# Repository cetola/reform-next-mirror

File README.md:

# MNT Reform Next

The original Open Hardware laptop, reloaded.

## Modular Concept

MNT Reform Next takes the MNT Reform family's modular approach a few steps further: The motherboard doesn't have any exterior ports, instead it breaks out all important signals in groups to FPC and JST-SH headers. The connectivity to the outside is implemented via user-exchangable Port Boards that increase repairability, customizability and future proofing of interfaces. The motherboard provides the system controller (RP2040 based), main (multi chemistry) LiFePO4/LiIon charger buck/boost controller, main 5V and 3V3 power rails and the SOM (Processor Module) interface, as well as a 4-lane PCIe M.2 connector for fast NVMe performance.

## Motherboard

Status: Version D-1 (code named "Reflex") designed, soldered, brought up on 2024-06-21.

Internal connectors:

- USB3+2 to Port Board One
- USB3+2 to Port Board Two
- 1 GBit Ethernet
- SD Card (4-bit)
- I2S Audio
- HDMI
- Display Power and Backlight PWM
- Serial UART for Debug
- Power Interface incl. I2C (for USB-C PD or direct power)
- 2x redundant/parallel Battery Packs (Power, Alert and I2C)
- Internal Keyboard Ports (USB and UART for standby mode)

Additional Features:

- RP2040 system controller
- 4-lane PCIe M.2 connector for NVMe
- RGB status LED
- 8-position DIP switch with several configuration options:
  - Power Override: Power on regardless of system controller output (useful for bringup without firmware)
  - Select battery chemistry/charge voltage (LiFePO4/LiIon)
  - Switch RP2040 USB to either SOM or external port for flashing
- USB2.0 hub
  - to provide enough internal USB2.0 ports for input devices and RP2040 communication

Power System:

- BQ25756 multi-chemistry charge buck/boost controller for 4S2P LiFePO4 or 4S2P LiIon batteries
- LM62460 for 6A of 5V power
- LM62460 for 6A of 3.3V power
- MAX1837EUT33+T for Standby 3v3 power

All main power rails work, and i.MX8MPlus Reform Processor module was used to boot Linux, which was operable via serial console (UART 2):

The system idles with only 2.3W power draw with the i.MX8MPlus module, meeting or power efficiency goals.

Motherboards physically fits in the prototype 3D printed case from december 2023:

## Processor Modules

MNT Reform Next supports a [variety of Processor Modules](https://mntre.com/modularity.html). The standard module is the RCORE with 8-core Rockchip RK3588 processor and Mali G610 GPU: https://source.mnt.re/reform/mnt-reform-rk3588-som/#mnt-reform-rcore-rk3588-som

## Port Boards

3 in total: Left, Right and Back sides:

- Standard Port Board One:
  - USB-C with USB3+2 signalling and USB Power Delivery
  - 1 GBit Ethernet (ix Industrial. Device will be shipped with a short ix to RJ45 jack dongle.)
  - MicroSD slot (bootable)
  - TLV320AIC3100 Soundchip with internal speaker driver/connector
  - Headset TRRS jack (stereo headphone driver and mono microphone support)
- Standard Port Board Two:
  - Full-size HDMI
  - 2x USB-C with USB3+2 signalling
  - 1x USB-A with USB3+2 signalling for legacy USB devices
- Standard Port Board Three:
  - WiFi/BT chipset and antennas

### Port Board One Dimensions / Specs

Port Board One is mounted on the left side of the case and is responsible for USB-C Power Delivery. When customizing this board, this functionality must be retained for powering the laptop. Copy the KiCAD source files as a starting point. There is a mechanical/spatial coupling with the keyboard that rests above the ports. Please take a look at the following drawing to see where the keyboard PCB is cut away. This defines the space that is available for ports. Any parts and connectors should not be taller than x mm above a 1.6mm PCB, because keycaps could collide with the components when being pressing down.

The electrical interfaces normally available to the left side are:

### Port Board Two Dimensions / Specs

Port Board Two is mounted on the right side of the case and mainly provides USB connectivity (3 ports), plus HDMI. Copy the KiCAD source files as a starting point. A similar mechanical/spatial coupling with the keyboard as with the Port Board One constrains the port placement, see the following drawing.

The electrical interfaces normally available to the right side are:

### Port Board Three Dimensions / Specs

Port Board Three hosts a WiFi/BT chipset by default. It receives USB2, SDIO and UART (with flow control) signals as well as 5V and 3V3 power from Processor Modules that support this (like the RCORE RK3588 module).

The default WiFi/BT implementation is based around the Ezurio Sterling-LWB5+ WiFi 5 with Bluetooth 5.2 SMT module. The chipset is Cypress CYW4373EUBGT, which has good Linux mainline driver support.

By default, this board doesn't expose any connectors to the outside. Instead, WiFi/BT antennas are mounted on it, and the port cover is made from an RF transmissive material to allow for good reception. But you can customize this board while making use of the available space under/behind the keyboard to add external ports, like external antenna connectors, or back-facing USB.

The electrical interfaces normally available to the back side are:

### Area Below the Keyboard

You have up to four millimeters of vertical space below the keyboard for extending port boards with low-profile components. 1mm or 0.8mm thick PCBs are recommended. You can also create boards that splice/transform/forward available FFC signals, such as USB (with hubs), I2C (with extenders), Ethernet (switch), etc. as long as they fit under the keyboard. There is some more space available between the through-hole pin rows of the keyboard. It is recommended to load your design as a STEP model into the provided FreeCAD laptop assembly file to check for any mechanical interference.

## Battery System

In Reform Next, the battery packs have 4 user replacable 18650 cells in series each. The packs are connected to the motherboard in parallel, so they are fully redundant. They have their own monitoring and balancing circuits and abstract all measurements like cell voltages, current, and alert states digitally over I2C. The main buck/boost charger resides on the motherboard. The coordination of the packs, the charger, and the USB-C power delivery living on Port Board one are implemented centrally in free software running on the RP2040 microcontroller on the motherboard. The default chemistry of the cells is LiFePO4. The chemistry can be switched to LiIon using DIP switches on the motherboard--this optional user choice trades longer runtime for less safety and environmental friendliness.

At the current state of development, the laptop successfully runs a Linux Wayland desktop from a single or two inserted battery packs. The small OLED display on top of the keyboard can show individual cell voltages and system voltage as well as dis/charging current.

The battery packs can be charged via USB-C power delivery from a off-the-shelf charger using the USB-C port on the left of the device.

## Case

The case, designed by Ana Dantas, has passed several revisions and is now (2024-09-24) ready for ordering as aluminum CNC milled parts.

- The case bottom integrates grooves to hold 8x 18650 batteries split into two parallel packs.
- The case bottom, as a large aluminum body, acts as the main heatsink for the CPU. The motherboard with CPU is mounted upside down with the CPU conducting heat to the case through a thermal pad. The motherboard is symmetrical and can also be flipped so that the CPU is on top, making it easier to work on the device for debugging.
- The case bottom also features a metric grid of screw threads for mounting standard and user defined electronics, a feature inspired by the "Peek array" in the original Novena OSHW laptop.
- The screen back integrates pockets for installing a camera module and mounting points for a FPC to JST-SH cable converter for the camera module.

## Mechanical Keyboard

The keyboard is an evolution/redesign of MNT Reform Keyboard V3 and integrates Pocket Reform features like RGB backlight and upgraded controller (RP2040). Keyswitches are Kailh Choc and keycaps are customized MBK Glows by FKcaps.

## Trackpad

The trackpad is an evolution of the multitouch glass trackpad option for classic MNT Reform based on the Azoteq TPS65 with IQS550 sensor. We revised it with a bigger, seamless frosted glass cover for which we sampled multiple glass suppliers and selected the one with the best haptics. We also added a strip of 3 mouse buttons below the trackpad to offer an alternative to multi finger gestures, including a middle mouse button that is important on Linux/BSD/Plan 9 desktops. The buttons are ultra low profile mechanical switches: Cherry MX ULP. As there are no commercially available keycaps for these switches, we developed our own based on the resources at [https://github.com/pashutk/Cherry_MX_ULP](https://github.com/pashutk/Cherry_MX_ULP).

## Camera Module

We developed the electronics of our OSHW standalone USB camera into a new version that can be installed inside of the MNT Reform Next. The sensor with autofocus lens is installed in a cavity in the screen back case above the display. The screen front part has a 2mm hole that the camera can look through. Below the display sits an adapter PCB that converts the flat/flex cable of the image sensor for a JST-SH based cable that transmits the MIPI-CSI signal through the right hinge of the laptop. A camera acquisition PCB that is part of the camera kit can be installed on the 4x4cm mounting grid below the keyboard. This converts the camera video signal into standard USB 3 or 2 UVC for use by the main processor. This module also has a connector for a hard powerdown switch and a LED that shows if it is powered. 

## Credits (So Far)

- Ana Dantas: Industrial Design
- Lukas "minute" Hartmann: Motherboard, Keyboard, Ports, Etc.
- Elen Eisendle: Battery Pack

## Copyright

All hardware design work in this repository is © 2024 [MNT Research GmbH](https://mntre.com), Berlin, Germany, and contributors (see Credits).

## License

All hardware sources are licensed under the [CERN Open Hardware Licence Version 2 - Strongly Reciprocal](https://ohwr.org/project/cernohl/wikis/uploads/002d0b7d5066e6b3829168730237bddb/cern_ohl_s_v2.txt).

## Funding

This project [receives funding by NLNet](https://nlnet.nl/project/MNT-Reform-Next/).

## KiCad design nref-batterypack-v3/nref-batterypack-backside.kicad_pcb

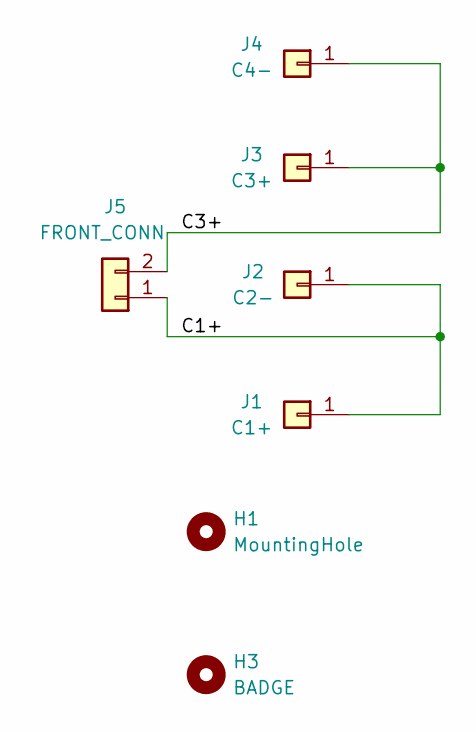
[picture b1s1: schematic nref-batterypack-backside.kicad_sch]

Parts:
H1: MountingHole; MountingHole_2.2mm_M2
H3: BADGE; nref-battback-badge
J1: C1+; Mill-Max_2036-X-57; MPN 2036-3-57-15-00-00-03-0; LCSC C20777560
J2: C2-; MYOUNG_MY-FJ-115; MPN MY-FJ-115II-R; LCSC C5457098
J3: C3+; Mill-Max_2036-X-57; MPN 2036-3-57-15-00-00-03-0; LCSC C20777560
J4: C4-; MYOUNG_MY-FJ-115; MPN MY-FJ-115II-R; LCSC C5457098
J5: FRONT_CONN; JST_SH_SM02B-SRSS-TB_1x02-1MP_P1.00mm_Horizontal; MPN SM02B-SRSS-TB; LCSC C160402

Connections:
/C1+: J1.1 (Pin_1_1), J2.1 (Pin_1_1), J5.1
/C3+: J3.1 (Pin_1_1), J4.1 (Pin_1_1), J5.2

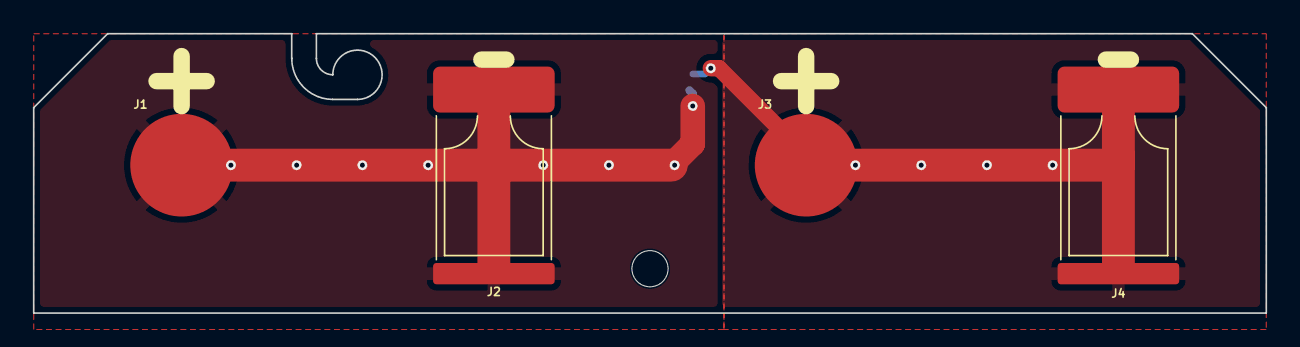
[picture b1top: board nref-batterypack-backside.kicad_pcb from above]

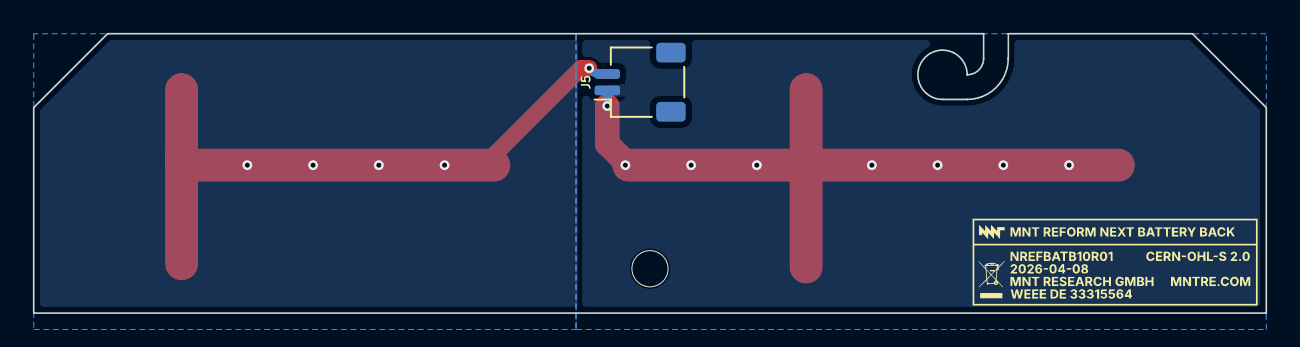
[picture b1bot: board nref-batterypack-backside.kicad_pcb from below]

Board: 4 copper layers, 75.0 x 17.0 mm, 7 parts (2 on the bottom side), 2 nets.

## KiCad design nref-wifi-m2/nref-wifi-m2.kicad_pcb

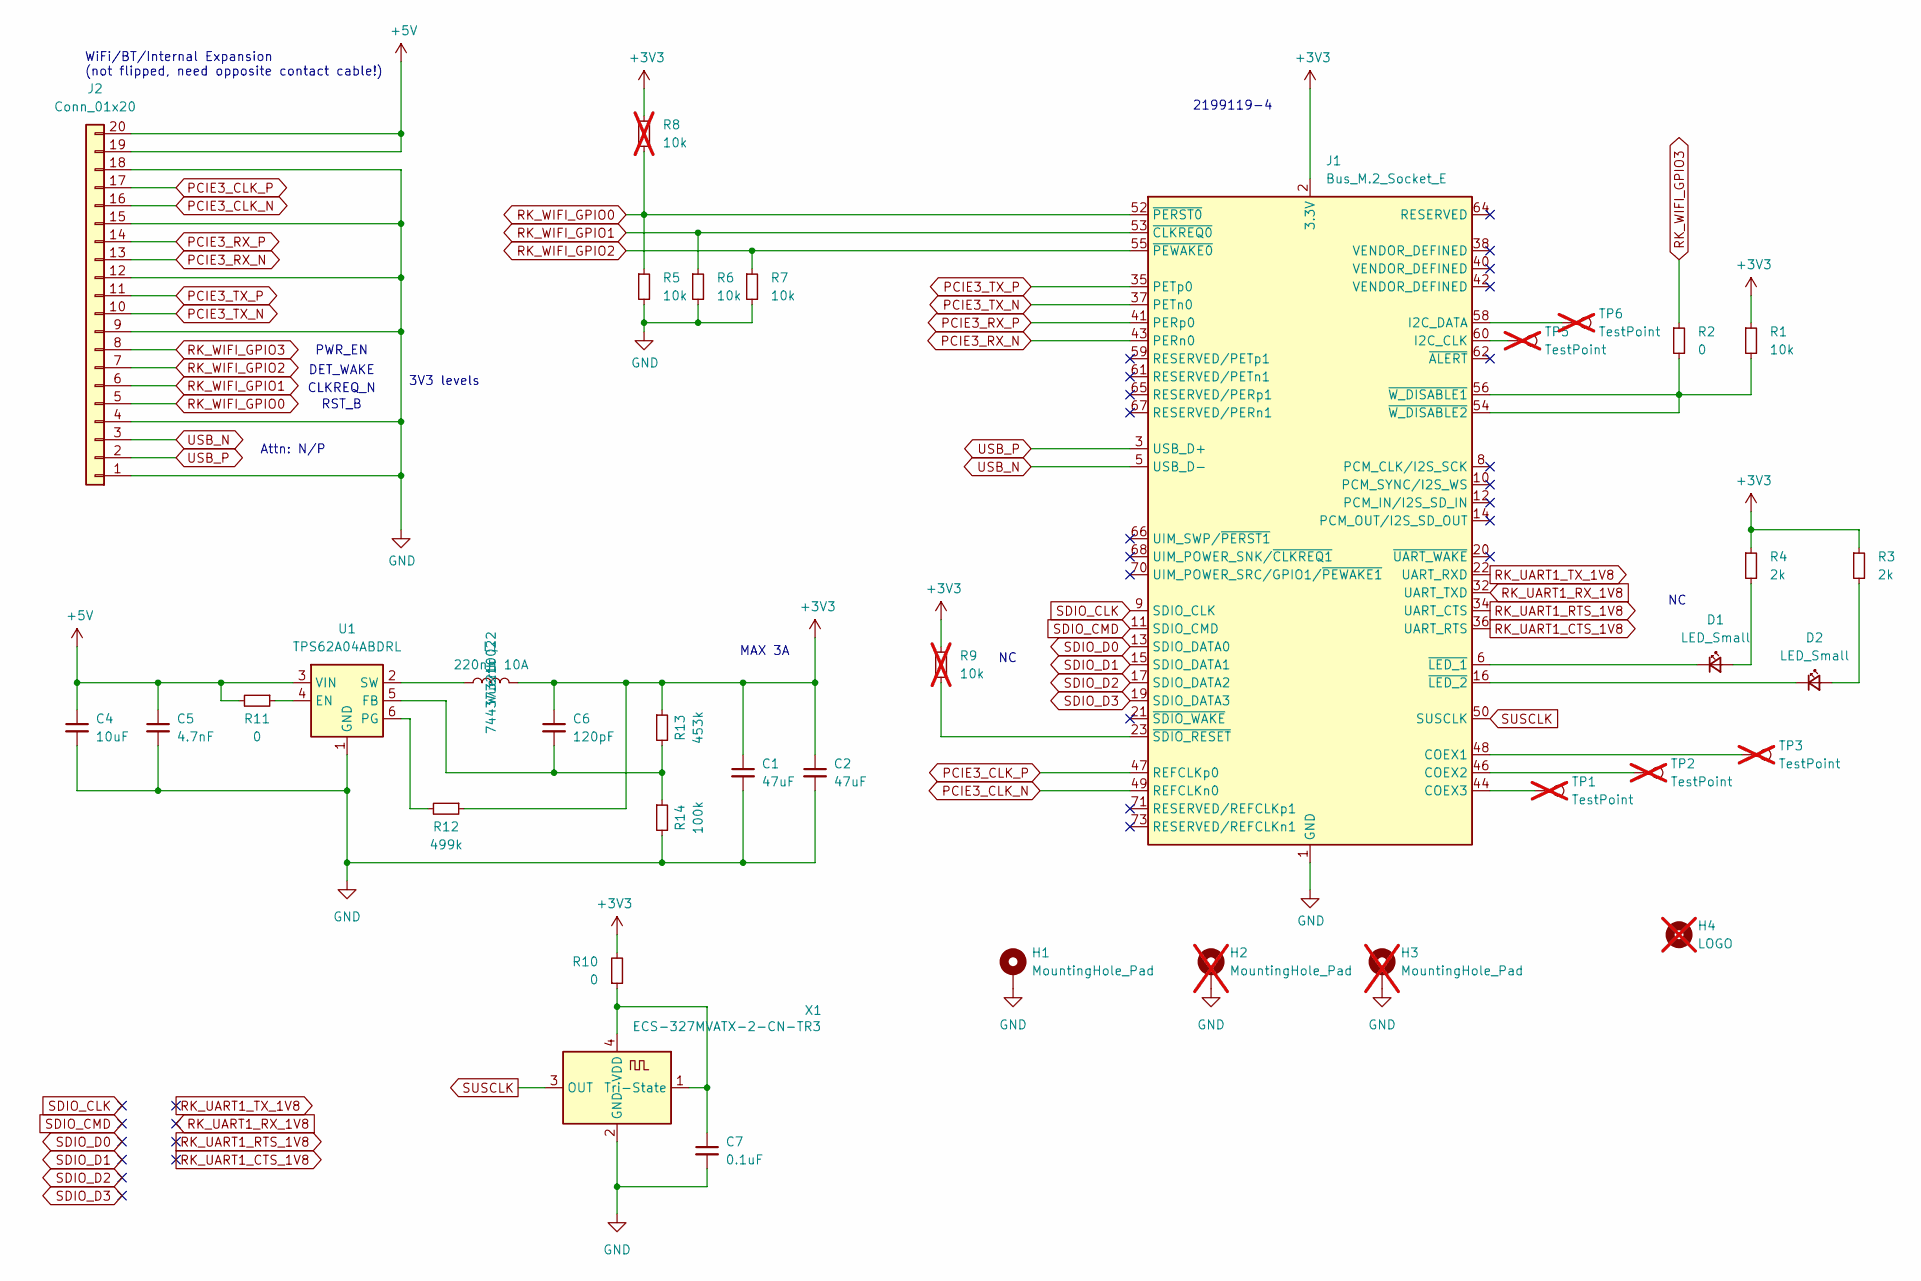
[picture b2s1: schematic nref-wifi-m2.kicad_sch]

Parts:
C1, C2: 47uF; C_1210_3225Metric; LCSC C84494
C4: 10uF; C_1210_3225Metric; LCSC C39232
C5: 4.7nF; C_0603_1608Metric; LCSC C85980
C6: 120pF; C_0603_1608Metric; LCSC C18438
C7: 0.1uF; C_0603_1608Metric; LCSC C77058
D1, D2: LED_Small; LED_0603_1608Metric; LCSC C5875723
H1: MountingHole_Pad; Mounting_Wuerth_WA-SMSI-M2_H1.5mm_9774015243; LCSC C22431324
H2, H3: MountingHole_Pad; MountingHole_2.2mm_M2_DIN965_Pad; not fitted
H4: LOGO; nref-wifi-m2-badge; not fitted
J1: Bus_M.2_Socket_E; TE_2199119-4; LCSC C5163551
J2: Conn_01x20; Hirose_FH12-20S-0.5SH_1x20-1MP_P0.50mm_Horizontal; LCSC C596730
L1: 220nH 10A; IND-SMD_L3.0-W3.0_FTC303020D; LCSC C5832405
R1, R5, R6, R7: 10k; R_0603_1608Metric; LCSC C25804
R2, R10, R11: 0; R_0603_1608Metric; LCSC C21189
R3, R4: 2k; R_0603_1608Metric; LCSC C22975
R8, R9: 10k; R_0603_1608Metric; LCSC C25804; not fitted
R12: 499k; R_0603_1608Metric; LCSC C26751
R13: 453k; R_0603_1608Metric; LCSC C25818
R14: 100k; R_0603_1608Metric; LCSC C25803
TP1, TP2, TP3, TP5, TP6: TestPoint; TestPoint_Pad_D1.0mm; not fitted
U1: TPS62A04ABDRL; SOT-563; LCSC C41447443
X1: ECS-327MVATX-2-CN-TR3; Oscillator_SMD_ECS_2520MV-xxx-xx-4Pin_2.5x2.0mm; LCSC C2901603

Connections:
+3V3: C1.1, C2.1, C6.1, J1.2 (3.3V), J1.4 (3.3V), J1.72 (3.3V), J1.74 (3.3V), L1.2, R1.1, R3.1, R4.1, R8.1, R9.1, R10.2, R12.1, R13.1
+5V: C4.1, C5.1, J2.19, J2.20, R11.2, U1.3 (VIN)
GND: C1.2, C2.2, C4.2, C5.2, C7.2, H1.1, H2.1, H3.1, J1.1 (GND), J1.7 (GND), J1.18 (GND), J1.33 (GND), J1.39 (GND), J1.45 (GND), J1.51 (GND), J1.57 (GND), J1.63 (GND), J1.69 (GND), J1.75 (GND), J2.1, J2.4, J2.9, J2.12, J2.15, J2.18, R5.2, R6.2, R7.2, R14.2, U1.1 (GND), X1.2 (GND)
unnamed: D1.2 (A), R4.2
unnamed: D1.1 (K), J1.6 (~LED_1)
unnamed: D2.2 (A), R3.2
unnamed: D2.1 (K), J1.16 (~LED_2)
unnamed: J1.48 (COEX1), TP3.1
unnamed: J1.46 (COEX2), TP2.1
unnamed: J1.44 (COEX3), TP1.1
unnamed: J1.60 (I2C_CLK), TP5.1
unnamed: J1.58 (I2C_DATA), TP6.1
unnamed: J1.23 (~SDIO_RESET), R9.2
unnamed: J1.54 (~W_DISABLE2), J1.56 (~W_DISABLE1), R1.2, R2.2
unnamed: R11.1, U1.4 (EN)
unnamed: C6.2, R13.2, R14.1, U1.5 (FB)
unnamed: R12.2, U1.6 (PG)
unnamed: L1.1, U1.2 (SW)
unnamed: C7.1, R10.1, X1.1 (Tri-State), X1.4 (VDD)
PCIE3_CLK_N: J1.49 (REFCLKn0), J2.16
PCIE3_CLK_P: J1.47 (REFCLKp0), J2.17
PCIE3_RX_N: J1.43 (PERn0), J2.13
PCIE3_RX_P: J1.41 (PERp0), J2.14
PCIE3_TX_N: J1.37 (PETn0), J2.10
PCIE3_TX_P: J1.35 (PETp0), J2.11
RK_UART1_CTS_1V8: J1.36 (UART_RTS)
RK_UART1_RTS_1V8: J1.34 (UART_CTS)
RK_UART1_RX_1V8: J1.32 (UART_TXD)
RK_UART1_TX_1V8: J1.22 (UART_RXD)
RK_WIFI_GPIO0: J1.52 (~PERST0), J2.5, R5.1, R8.2
RK_WIFI_GPIO1: J1.53 (~CLKREQ0), J2.6, R6.1
RK_WIFI_GPIO2: J1.55 (~PEWAKE0), J2.7, R7.1
RK_WIFI_GPIO3: J2.8, R2.1
SDIO_CLK: J1.9 (SDIO_CLK)
SDIO_CMD: J1.11 (SDIO_CMD)
SDIO_D0: J1.13 (SDIO_DATA0)
SDIO_D1: J1.15 (SDIO_DATA1)
SDIO_D2: J1.17 (SDIO_DATA2)
SDIO_D3: J1.19 (SDIO_DATA3)
SUSCLK: J1.50 (SUSCLK), X1.3 (OUT)
USB_N: J1.5 (USB_D-), J2.3
USB_P: J1.3 (USB_D+), J2.2

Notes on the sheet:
3V3 levels
RST_B
PWR_EN
2199119-4
WiFi/BT/Internal Expansion (not flipped, need opposite contact cable!)
MAX 3A
DET_WAKE
CLKREQ_N
Attn: N/P

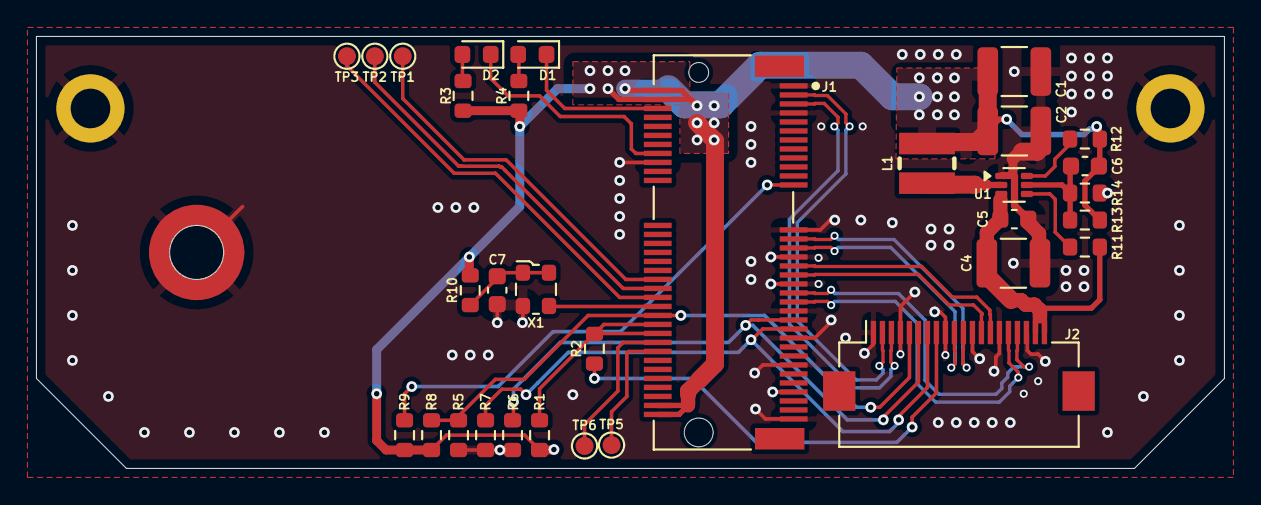
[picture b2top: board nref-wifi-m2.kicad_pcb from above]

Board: 4 copper layers, 66.0 x 24.0 mm, 36 parts (1 on the bottom side), 32 nets.

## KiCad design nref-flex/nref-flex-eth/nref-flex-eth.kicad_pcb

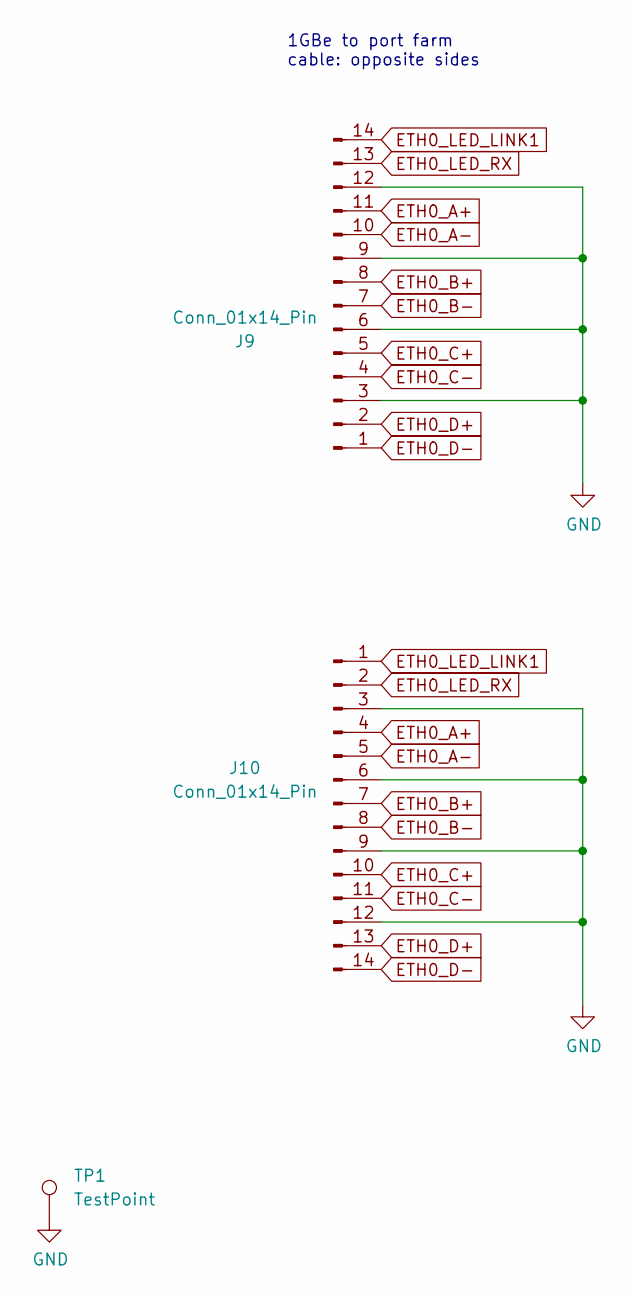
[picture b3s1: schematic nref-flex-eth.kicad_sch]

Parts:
J9, J10: Conn_01x14_Pin; Hirose_FH12-14S-0.5SH_1x14-1MP_P0.50mm_Horizontal
TP1: TestPoint; TestPoint_Pad_D1.0mm

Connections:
ETH0_A+: J9.11, J10.4
ETH0_A-: J9.10, J10.5
ETH0_B+: J9.8, J10.7
ETH0_B-: J9.7, J10.8
ETH0_C+: J9.5, J10.10
ETH0_C-: J9.4, J10.11
ETH0_D+: J9.2, J10.13
ETH0_D-: J9.1, J10.14
ETH0_LED_LINK1: J9.14, J10.1
ETH0_LED_RX: J9.13, J10.2
GND: J9.3, J9.6, J9.9, J9.12, J10.3, J10.6, J10.9, J10.12, TP1.1

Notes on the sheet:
1GBe to port farm cable: opposite sides

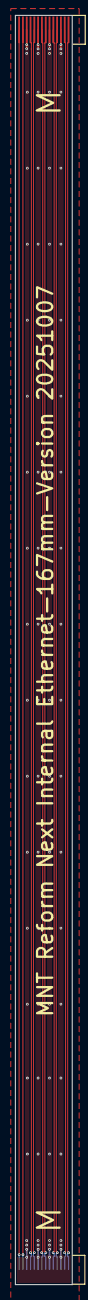
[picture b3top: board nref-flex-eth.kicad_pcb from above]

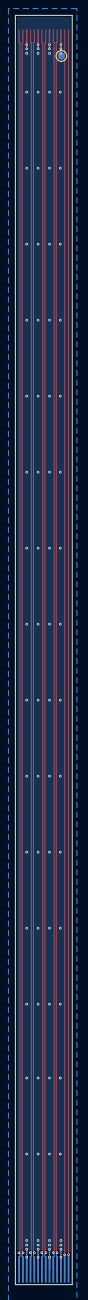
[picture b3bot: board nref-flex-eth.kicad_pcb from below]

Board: 2 copper layers, 7.5 x 167.0 mm, 3 parts (2 on the bottom side), 11 nets.

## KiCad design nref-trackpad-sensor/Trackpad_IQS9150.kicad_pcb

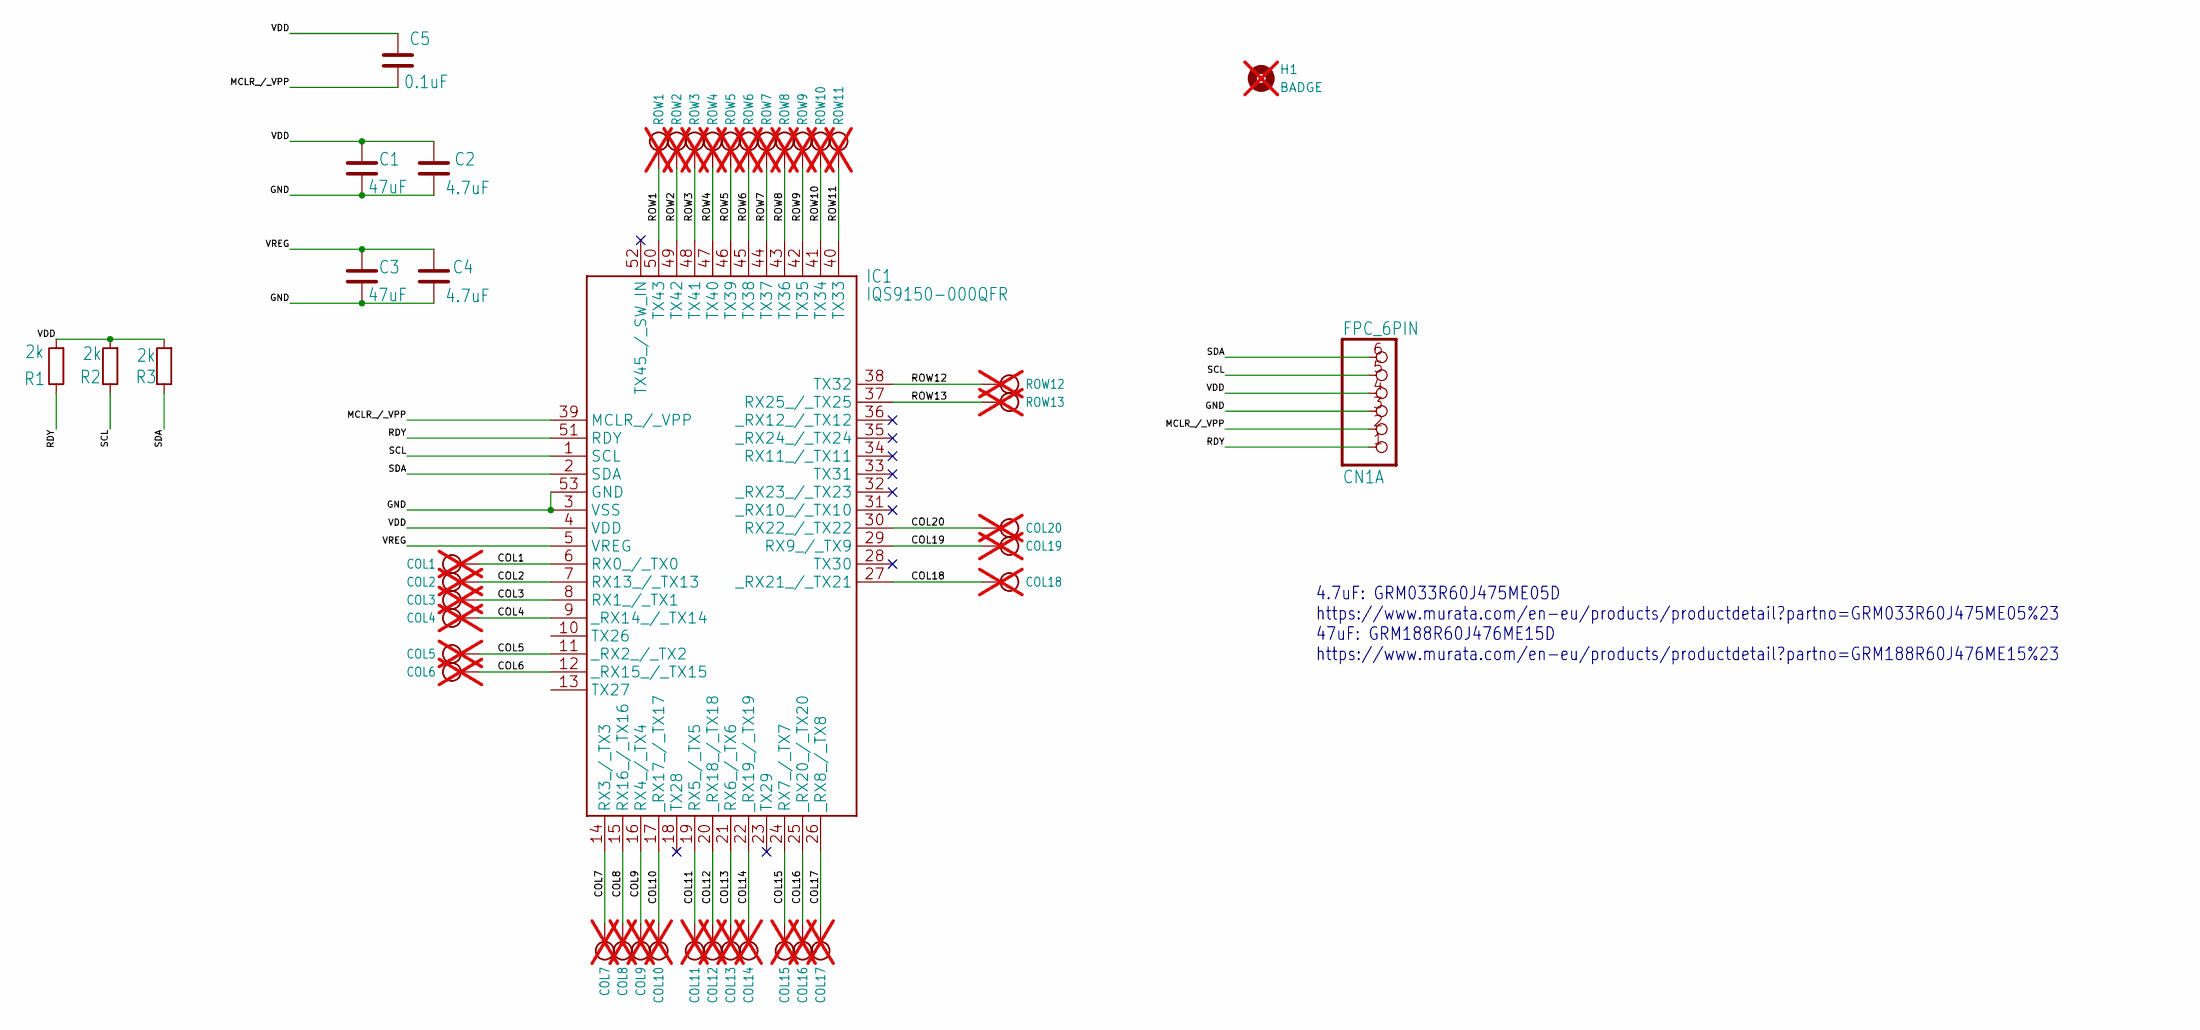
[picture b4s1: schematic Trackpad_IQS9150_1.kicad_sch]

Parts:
C1, C3: 47uF; C_0603_1608Metric; MPN GRM188R60J476ME15D; LCSC C140782
C2, C4: 4.7uF; C_0402_1005Metric; MPN CL05A475MP5NRNC; LCSC C23733
C5: 0.1uF; C_0402_1005Metric; MPN CL05B104KO5NNNC; LCSC C1525
CN1: FPC_6PIN; Hirose_FH12-6S-0.5SH_1x06-1MP_P0.50mm_Horizontal; MPN FH12-6S-0.5SH(55); LCSC C202118
COL1, COL2, COL3, COL4, COL5, COL6, COL7, COL8, COL9, COL10, COL11, COL12, COL13, COL14, COL15, COL16, COL17, COL18, COL19, COL20: TESTPOINTPAD_0_5MM; PAD_0_5MM; not fitted
H1: BADGE; nref-tpsensor-badge; not fitted
IC1: IQS9150-000QFR; IQS9150000QFR; MPN IQS9150-000QFR; LCSC C34066848
R1, R2, R3: 2k; R_0402_1005Metric; MPN 0402WGF2001TCE; LCSC C4109
ROW1, ROW2, ROW3, ROW4, ROW5, ROW6, ROW7, ROW8, ROW9, ROW10, ROW11, ROW12, ROW13: TESTPOINTPAD_0_5MM; PAD_0_5MM; not fitted

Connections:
/Trackpad_IQS9150_1/COL1: COL1.P1 (P1_P1), IC1.6 (RX0_/_TX0)
/Trackpad_IQS9150_1/COL2: COL2.P1 (P1_P1), IC1.7 (RX13_/_TX13)
/Trackpad_IQS9150_1/COL3: COL3.P1 (P1_P1), IC1.8 (RX1_/_TX1)
/Trackpad_IQS9150_1/COL4: COL4.P1 (P1_P1), IC1.9 (_RX14_/_TX14)
/Trackpad_IQS9150_1/COL5: COL5.P1 (P1_P1), IC1.11 (_RX2_/_TX2)
/Trackpad_IQS9150_1/COL6: COL6.P1 (P1_P1), IC1.12 (_RX15_/_TX15)
/Trackpad_IQS9150_1/COL7: COL7.P1 (P1_P1), IC1.14 (RX3_/_TX3)
/Trackpad_IQS9150_1/COL8: COL8.P1 (P1_P1), IC1.15 (RX16_/_TX16)
/Trackpad_IQS9150_1/COL9: COL9.P1 (P1_P1), IC1.16 (RX4_/_TX4)
/Trackpad_IQS9150_1/COL10: COL10.P1 (P1_P1), IC1.17 (_RX17_/_TX17)
/Trackpad_IQS9150_1/COL11: COL11.P1 (P1_P1), IC1.19 (RX5_/_TX5)
/Trackpad_IQS9150_1/COL12: COL12.P1 (P1_P1), IC1.20 (_RX18_/_TX18)
/Trackpad_IQS9150_1/COL13: COL13.P1 (P1_P1), IC1.21 (RX6_/_TX6)
/Trackpad_IQS9150_1/COL14: COL14.P1 (P1_P1), IC1.22 (_RX19_/_TX19)
/Trackpad_IQS9150_1/COL15: COL15.P1 (P1_P1), IC1.24 (RX7_/_TX7)
/Trackpad_IQS9150_1/COL16: COL16.P1 (P1_P1), IC1.25 (_RX20_/_TX20)
/Trackpad_IQS9150_1/COL17: COL17.P1 (P1_P1), IC1.26 (_RX8_/_TX8)
/Trackpad_IQS9150_1/COL18: COL18.P1 (P1_P1), IC1.27 (_RX21_/_TX21)
/Trackpad_IQS9150_1/COL19: COL19.P1 (P1_P1), IC1.29 (RX9_/_TX9)
/Trackpad_IQS9150_1/COL20: COL20.P1 (P1_P1), IC1.30 (RX22_/_TX22)
/Trackpad_IQS9150_1/GND: C1.2, C2.2, C3.2, C4.2, CN1.3, IC1.3 (VSS), IC1.53 (GND)
/Trackpad_IQS9150_1/MCLR_/_VPP: C5.2, CN1.2, IC1.39 (MCLR_/_VPP)
/Trackpad_IQS9150_1/RDY: CN1.1, IC1.51 (RDY), R1.1
/Trackpad_IQS9150_1/ROW1: IC1.50 (TX43), ROW1.P1 (P1_P1)
/Trackpad_IQS9150_1/ROW2: IC1.49 (TX42), ROW2.P1 (P1_P1)
/Trackpad_IQS9150_1/ROW3: IC1.48 (TX41), ROW3.P1 (P1_P1)
/Trackpad_IQS9150_1/ROW4: IC1.47 (TX40), ROW4.P1 (P1_P1)
/Trackpad_IQS9150_1/ROW5: IC1.46 (TX39), ROW5.P1 (P1_P1)
/Trackpad_IQS9150_1/ROW6: IC1.45 (TX38), ROW6.P1 (P1_P1)
/Trackpad_IQS9150_1/ROW7: IC1.44 (TX37), ROW7.P1 (P1_P1)
/Trackpad_IQS9150_1/ROW8: IC1.43 (TX36), ROW8.P1 (P1_P1)
/Trackpad_IQS9150_1/ROW9: IC1.42 (TX35), ROW9.P1 (P1_P1)
/Trackpad_IQS9150_1/ROW10: IC1.41 (TX34), ROW10.P1 (P1_P1)
/Trackpad_IQS9150_1/ROW11: IC1.40 (TX33), ROW11.P1 (P1_P1)
/Trackpad_IQS9150_1/ROW12: IC1.38 (TX32), ROW12.P1 (P1_P1)
/Trackpad_IQS9150_1/ROW13: IC1.37 (RX25_/_TX25), ROW13.P1 (P1_P1)
/Trackpad_IQS9150_1/SCL: CN1.5, IC1.1 (SCL), R2.1
/Trackpad_IQS9150_1/SDA: CN1.6, IC1.2 (SDA), R3.1
/Trackpad_IQS9150_1/VDD: C1.1, C2.1, C5.1, CN1.4, IC1.4 (VDD), R1.2, R2.2, R3.2
/Trackpad_IQS9150_1/VREG: C3.1, C4.1, IC1.5 (VREG)

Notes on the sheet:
4.7uF: GRM033R60J475ME05D https://www.murata.com/en-eu/products/productdetail?partno=GRM033R60J475ME05%23 47uF: GRM188R60J476ME15D https://www.murata.com/en-eu/products/productdetail?partno=GRM188R60J476ME15%23

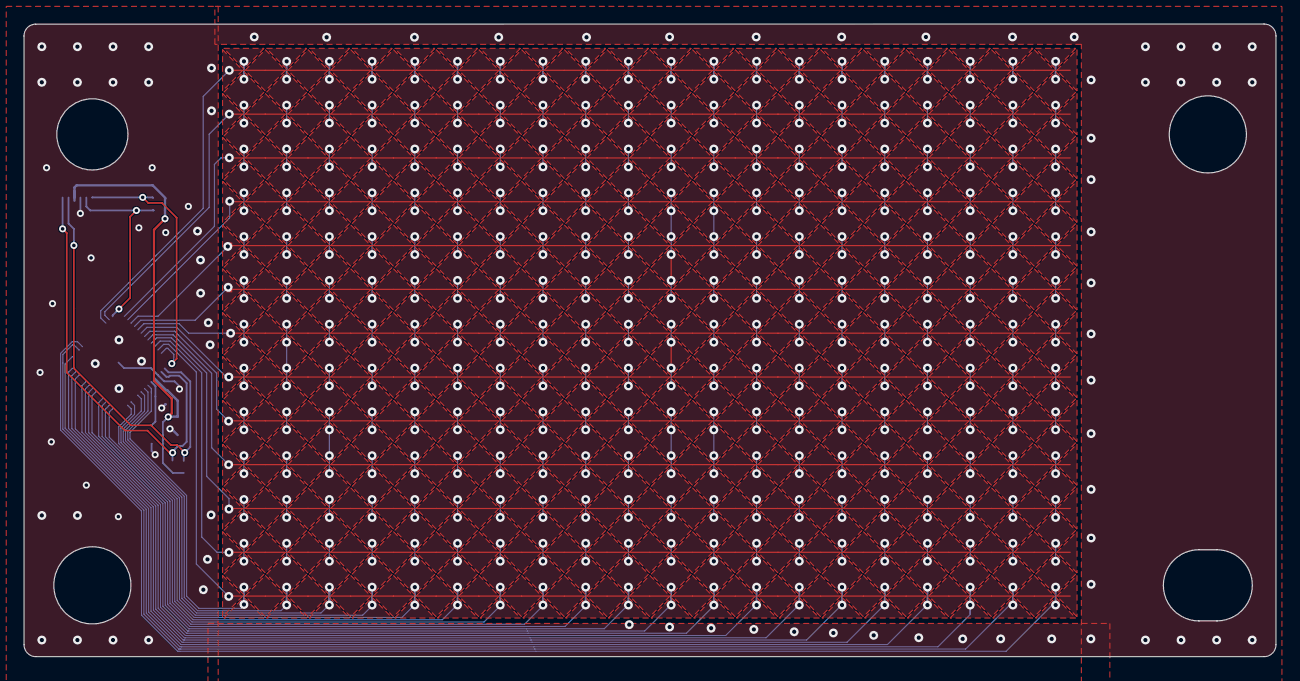
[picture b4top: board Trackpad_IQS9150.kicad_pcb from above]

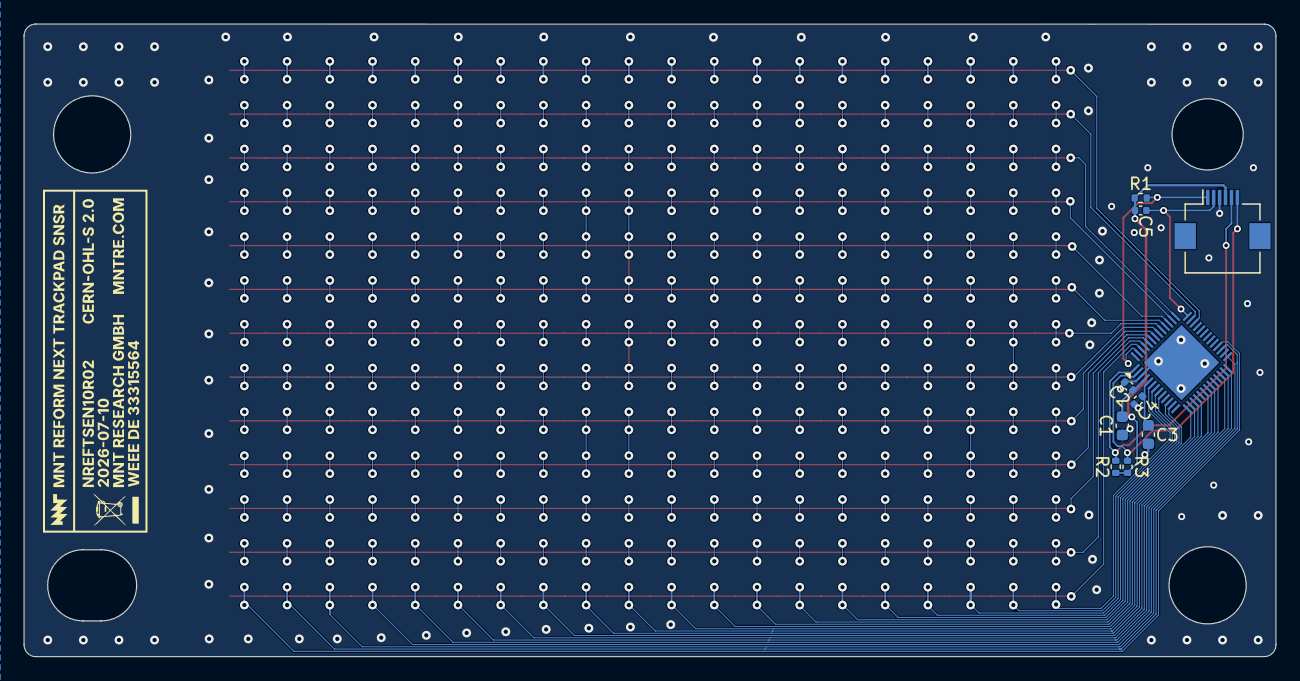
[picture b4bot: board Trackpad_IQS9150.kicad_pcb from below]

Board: 2 copper layers, 105.5 x 53.3 mm, 44 parts (31 on the bottom side), 40 nets.

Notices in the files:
nref-ports-two/nref-ports-two.kicad_sch:
License: CERN OHL-S 2.0
